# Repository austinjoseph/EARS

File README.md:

# EARS

### Idea 1:

### Electromechanical Automatic Relief System

Visual Pressure Sensor (for verification)

IC Pressure Sensor

Solenoid (for actuation)

MCU (STM32L152)

This system accepts gas from a pressurized system (air compressor, bike pump etc.) and holds pressure until ~75 psi is reached, at this point the solenoid is actuated in short burts to reduce the pressure in the chamber.  It will be built with PVC and cheap parts as a proof of concept.  A chamber can be made of arbitrary lengths of 1-2" PVC with T's and caps modified to allow sensors be placed inside the pressure chamber.

We've chose this design for it's simplicity, usefullness and scaling capablitity (it could be improved and used in industrial processes).

---

### Idea 2:

### Artificially Intelliget Robot Swarm

IMU For Position and Orientation

Infrared camera array for collision detection

GPS for position

2 DC Motors

MCU (STM32L152)

This system would require that the control system be weighted and placed inside a plastic ball.  The DC motors would control an axis of rotation each.  The control board would be allowed to spin freely via a gyro.  The device could then move itself around by spinning a combination of both DC motors.  In cunjunction with several other similar robots they could be 'trained' to move in unison for carrying loads or moved chaoticly for entertainment.

This is needlessly complicated for questionable value.

---

### Idea 3:

### Single Point Magnetic Field Viewer

Magentometer to meassure the strength and relative polarity of nearby magnetic fields.

LEDs to show the Magnetic Field parametes.

1860 LiPo battery for portability.

This system would indicate the polarity via the different colored LEDs and field strength by the brightness of the LEDs.  This would be a cheap device for helping people visualize the size, strength, and shape of magentic fields in their environment.

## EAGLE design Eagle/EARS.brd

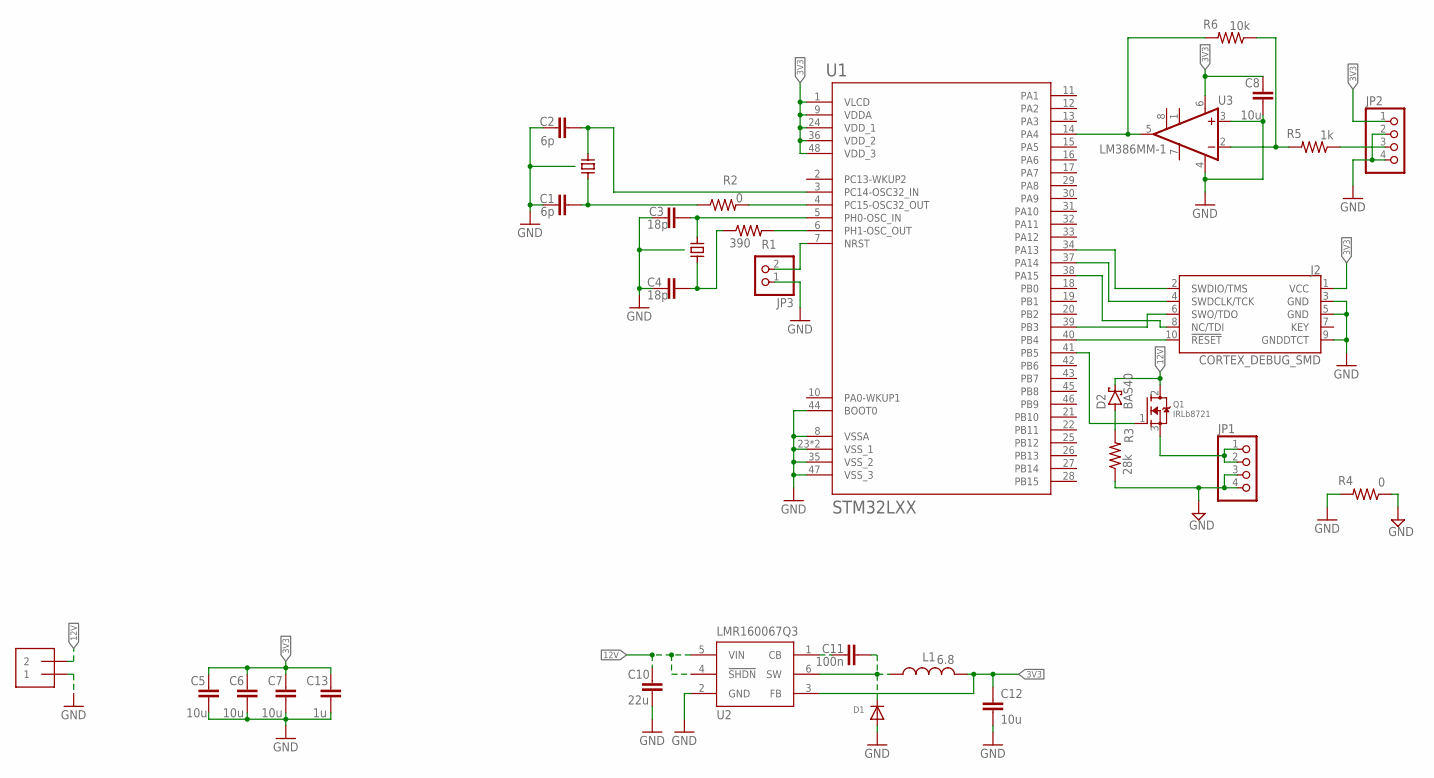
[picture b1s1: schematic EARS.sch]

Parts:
C1, C2: 6p; C0603
C3, C4: 18p; C0603
C5, C6, C7, C8, C12: 10u; C0603
C10: 22u; C0603
C11: 100n; C0603
C13: 1u; C0603
D1: DIODESMA; SMADIODE
D2: BAS40; SOT23
J1: 1X2-3.5MM
J2: CORTEX_DEBUG_SMD; SAMTECH_FTSH-105-01
JP1, JP2: PINHD-1X4; 1X04
JP3: PINHD-1X2; 1X02
L1: 6.8; L3216C
Q1: IRLb8721; TO220V
R1: 390; R0603
R2, R4: 0; R0603
R3: 28k; R0603
R5: 1k; R0603
R6: 10k; R0603
U1: STM32LXX; UFQFPN48
U2: LMR160067Q3; TI_SOT6
U3: LM386MM-1; MMSOP08
X1: ECX_34G; 3.2X1.5_SC
X2: FL0800011Q; 3.2X2.5_SSC

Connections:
3V3: C5.2, C6.2, C7.2, C8.2, C12.1, C13.2, J2.1 (VCC), JP2.1, L1.2, U1.1 (VLCD), U1.9 (VDDA), U1.24 (VDD_1), U1.36 (VDD_2), U1.48 (VDD_3), U2.3 (FB), U3.6 (VS)
8M0X_OUT: C4.2, R1.1, X2.3 (C2)
8MOX_IN: C3.2, U1.5 (PH0-OSC_IN), X2.1 (C1)
12V: C10.2, D2.3 (C), J1.2, Q1.2 (D), U2.4 (!SHDN!), U2.5 (VIN)
!RESET!: J2.10 (!RESET), U1.40 (PB4)
AGND: JP1.3, JP1.4, R3.1, R4.1
FB: R5.2, R6.1, U3.2 (-IN)
FLYBACK: D2.1 (A), R3.2
GND: C1.1, C2.1, C3.1, C4.1, C5.1, C6.1, C7.1, C8.1, C10.1, C12.2, C13.1, D1.A, J1.1, J2.3 (GND), J2.5 (GND), J2.9 (GNDDTCT), JP2.2, JP2.4, JP3.1, R4.2, U1.8 (VSSA), U1.23 (VSS_1), U1.35 (VSS_2), U1.44 (BOOT0), U1.47 (VSS_3), U1.T1 (VSS_1), U2.2 (GND), U3.3 (+IN), U3.4 (GND), X1.GND, X2.2, X2.4
LMR_CB: C11.1, U2.1 (CB)
LMR_SW: C11.2, D1.C, L1.1, U2.6 (SW)
MCU_P4: R2.2, U1.4 (PC15-OSC32_OUT)
MCU_P6: R1.2, U1.6 (PH1-OSC_OUT)
NC: J2.8 (NC/TDI), U1.38 (PA15)
NPN: JP1.1, JP1.2, Q1.3 (S)
NPN_DRV: Q1.1 (G), U1.41 (PB5)
NRST: JP3.2, U1.7 (NRST)
OSC32_IN: C1.2, R2.1, X1.C2
OSC32_OUT: C2.2, U1.3 (PC14-OSC32_IN), X1.C1
PRESSURE: R6.2, U1.14 (PA4), U3.5 (OUT)
PRSR_IN: JP2.3, R5.1
SWDCLK: J2.4 (SWDCLK/TCK), U1.37 (PA14)
SWDIO: J2.2 (SWDIO/TMS), U1.34 (PA13)
SWO: J2.6 (SWO/TDO), U1.39 (PB3)

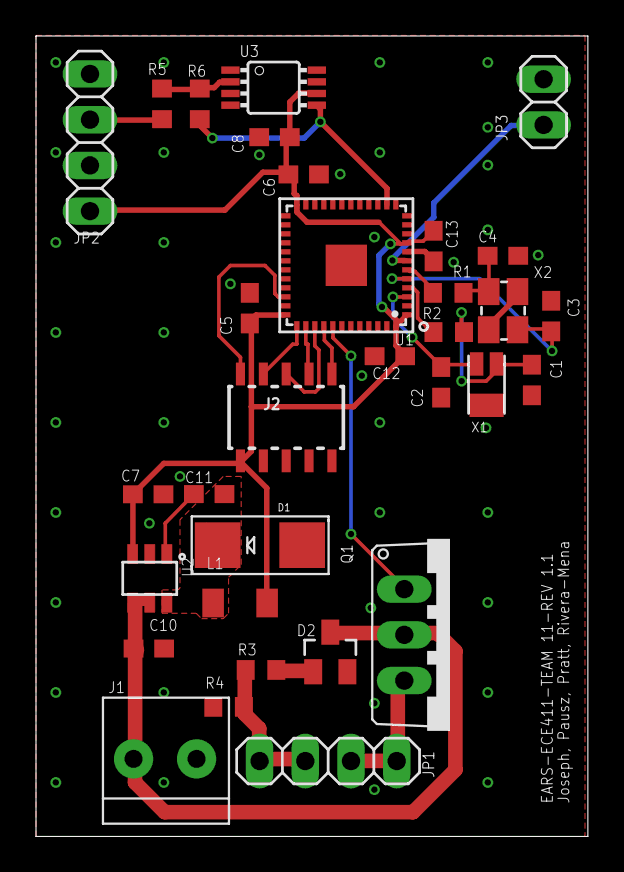
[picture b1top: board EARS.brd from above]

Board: 2 copper layers, 30.7 x 44.5 mm, 32 parts (0 on the bottom side), 24 nets.

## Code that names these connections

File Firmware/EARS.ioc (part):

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Mcu.Name=STM32L151C(6-8-B)Ux
Mcu.Package=UFQFPN48
Mcu.UserName=STM32L151C6Ux
PA13.Mode=JTAG_5_pins
PA13.Signal=SYS_JTMS-SWDIO
PA14.Mode=JTAG_5_pins
PA14.Signal=SYS_JTCK-SWCLK
PA15.Mode=JTAG_5_pins
PA15.Signal=SYS_JTDI
PA4.Mode=IN4
PA4.Signal=ADC_IN4
PB3.Mode=JTAG_5_pins
PB3.Signal=SYS_JTDO-TRACESWO
PB4.Mode=JTAG_5_pins
PB4.Signal=SYS_JTRST
PB5.Signal=GPIO_Output
PC14-OSC32_IN.Mode=LSE-External-Oscillator
PC14-OSC32_IN.Signal=RCC_OSC32_IN
PC15-OSC32_OUT.Mode=LSE-External-Oscillator
PC15-OSC32_OUT.Signal=RCC_OSC32_OUT
PH0-OSC_IN.Mode=HSE-External-Oscillator
PH0-OSC_IN.Signal=RCC_OSC_IN
PH1-OSC_OUT.Mode=HSE-External-Oscillator
PH1-OSC_OUT.Signal=RCC_OSC_OUT
RCC.HSE_VALUE=8000000
RCC.SYSCLKFreq_VALUE=2097000
board=custom

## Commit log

2019-10-07 Added empty License.
2019-10-14 Added MIT License Text
2019-10-14 Deleted Date License
2019-10-14 Added first idea, no formatting.
2019-10-14 formatting
2019-10-17 Changed acronym, Included actual MCU
2019-10-17 Added second idea, some formatting.
2019-10-17 More Formatting
2019-10-18 Update Requirements.md
    fixed some spelling errors
2019-10-21 Included customer (Andrew) requirements. Included suggested requirements.
2019-10-21 Added, Directories, BOM, Datasheets.
2019-10-21 Added WPR, folder.
2019-10-24 Update Requirements.md
    Changing formatting for the rubric
2019-10-24 Update Requirements.md
    small changes - spark gap ---> ignition system
2019-10-24 Formatting.
2019-10-31 Create Parts & URLs
    Working directory for keeping track of the parts used in the Schematic.
2019-10-31 Add files via upload
    Initial Schematic for the EARS board.
2019-10-31 Added firmware directory
2019-10-31 Add files via upload
    Added step down regulator to Schematic.
2019-11-06 Created Project Schedule.
2019-11-07 Initial Layout, fixed schematic.
2019-11-07 Housekeeping.
2019-11-07 Included eagle library, moved eagle files to eagle directory.
2019-11-07 Juan finished it!
2019-11-14 Read the file name.
    Isn't the name descriptive enough?
2019-11-14 EARS Controller
    Top Level EARS Controller Board.
2019-11-20 Worked on board layout and wire routing.
2019-11-21 Added text to identify the board.
2019-11-21 Create Board Review.md
    Notes from our board review session with the C3 Team.
2019-11-21 Fixed schematics, added sense circuitry, added solenoid switch circuitry. Finished layout Rev 1.1
2019-11-21 C6git statusgit status1git status
2019-11-21 Fixed Silk Screen
2019-11-22 Added Parts From Schematic
    Some parts are still missing and there are a few I was unsure of the specs or how to find. Anything I was unsure of I put in the notes section. There were also a few parts that are out of stock so we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
2019-11-27 Updated BOM
    Found the correct size caps and most other parts as well. Still missing 3 parts and 1 or 2 that might not be exactly the right part.
2019-11-27 Cleared up value issues, added links for missing parts.
2019-12-03 Updated BOM
    Still missing 22uF caps we need 4, could not find any 0603s or smaller anywhere.
2019-12-06 Added Honeywell Datasheet
2019-12-07 Added updated firmare for new MCU
2019-12-10 Added updated firmware.
2019-12-10 Wrong Datasheet.
2019-12-10 Correct MCU Datasheet
2019-12-11 Organized and Finalized BOM
2019-12-11 Pics of brd/sch
2019-12-11 Pic of BOM
2019-12-11 Board Pic
2019-12-12 Added code snippet photo.

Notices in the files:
parts and their libraries:
SparkFun-Connectors: Licensing: Creative Commons ShareAlike 4.0 International - https://creativecommons.org/licenses/by-sa/4.0
